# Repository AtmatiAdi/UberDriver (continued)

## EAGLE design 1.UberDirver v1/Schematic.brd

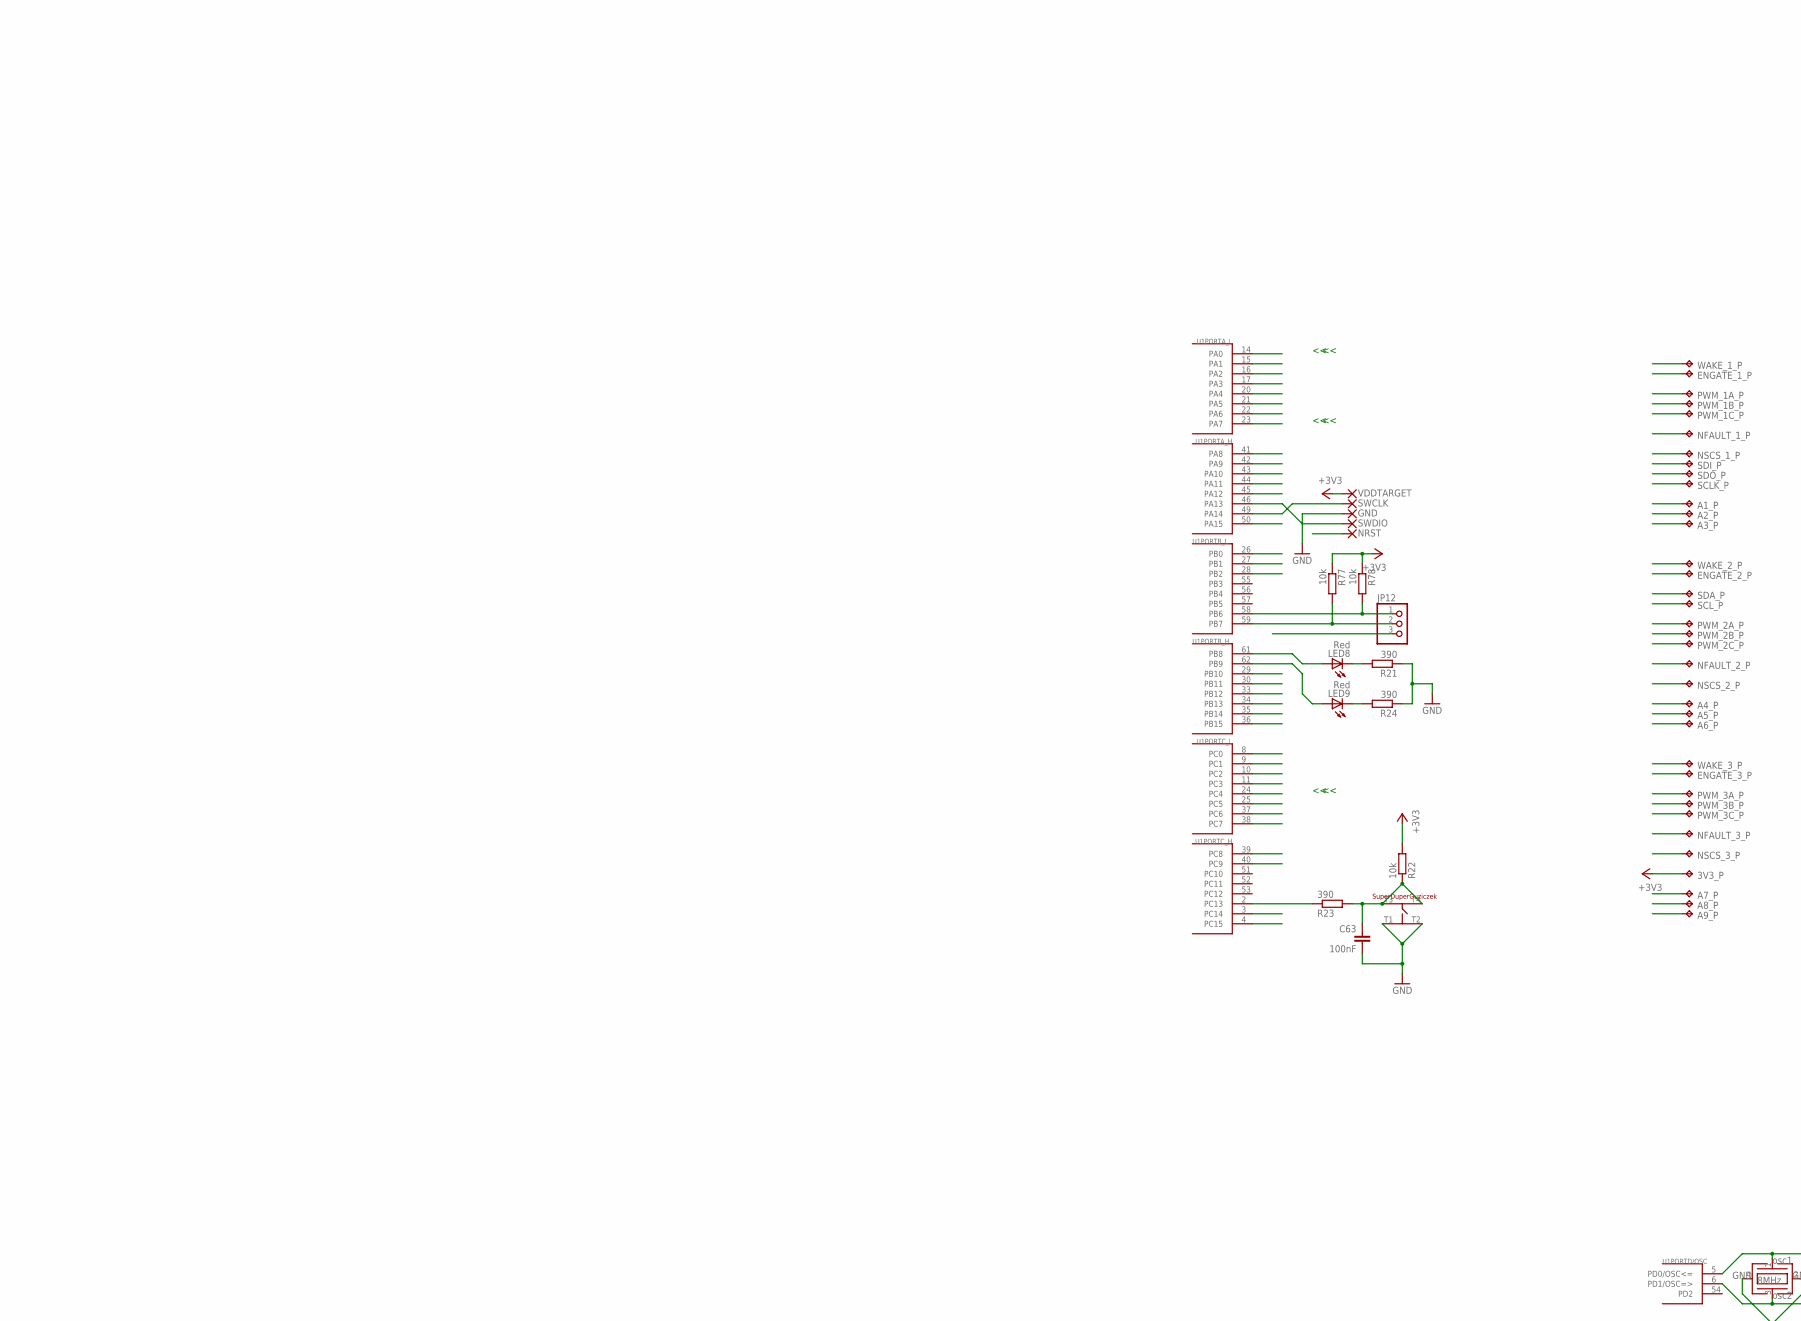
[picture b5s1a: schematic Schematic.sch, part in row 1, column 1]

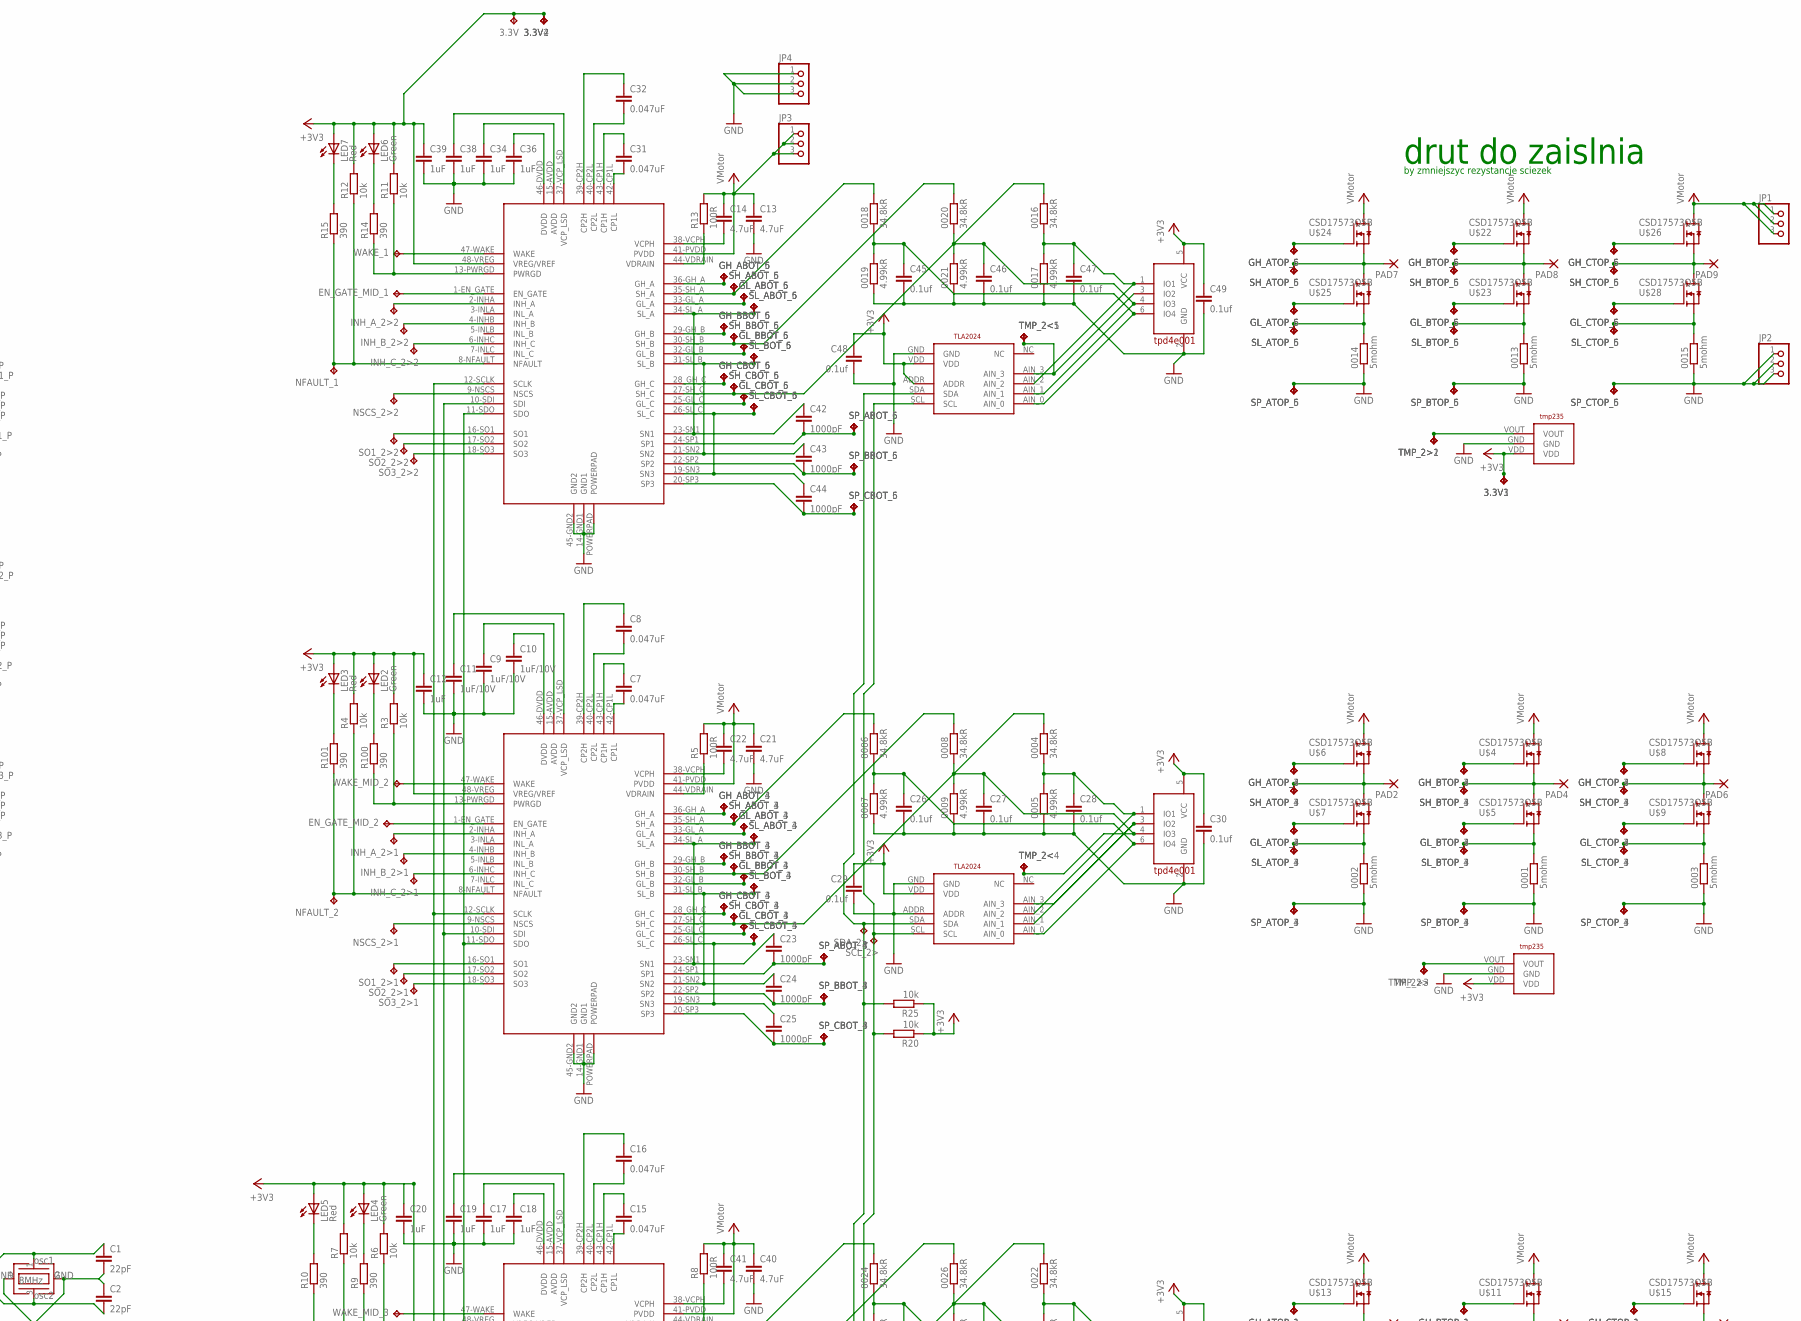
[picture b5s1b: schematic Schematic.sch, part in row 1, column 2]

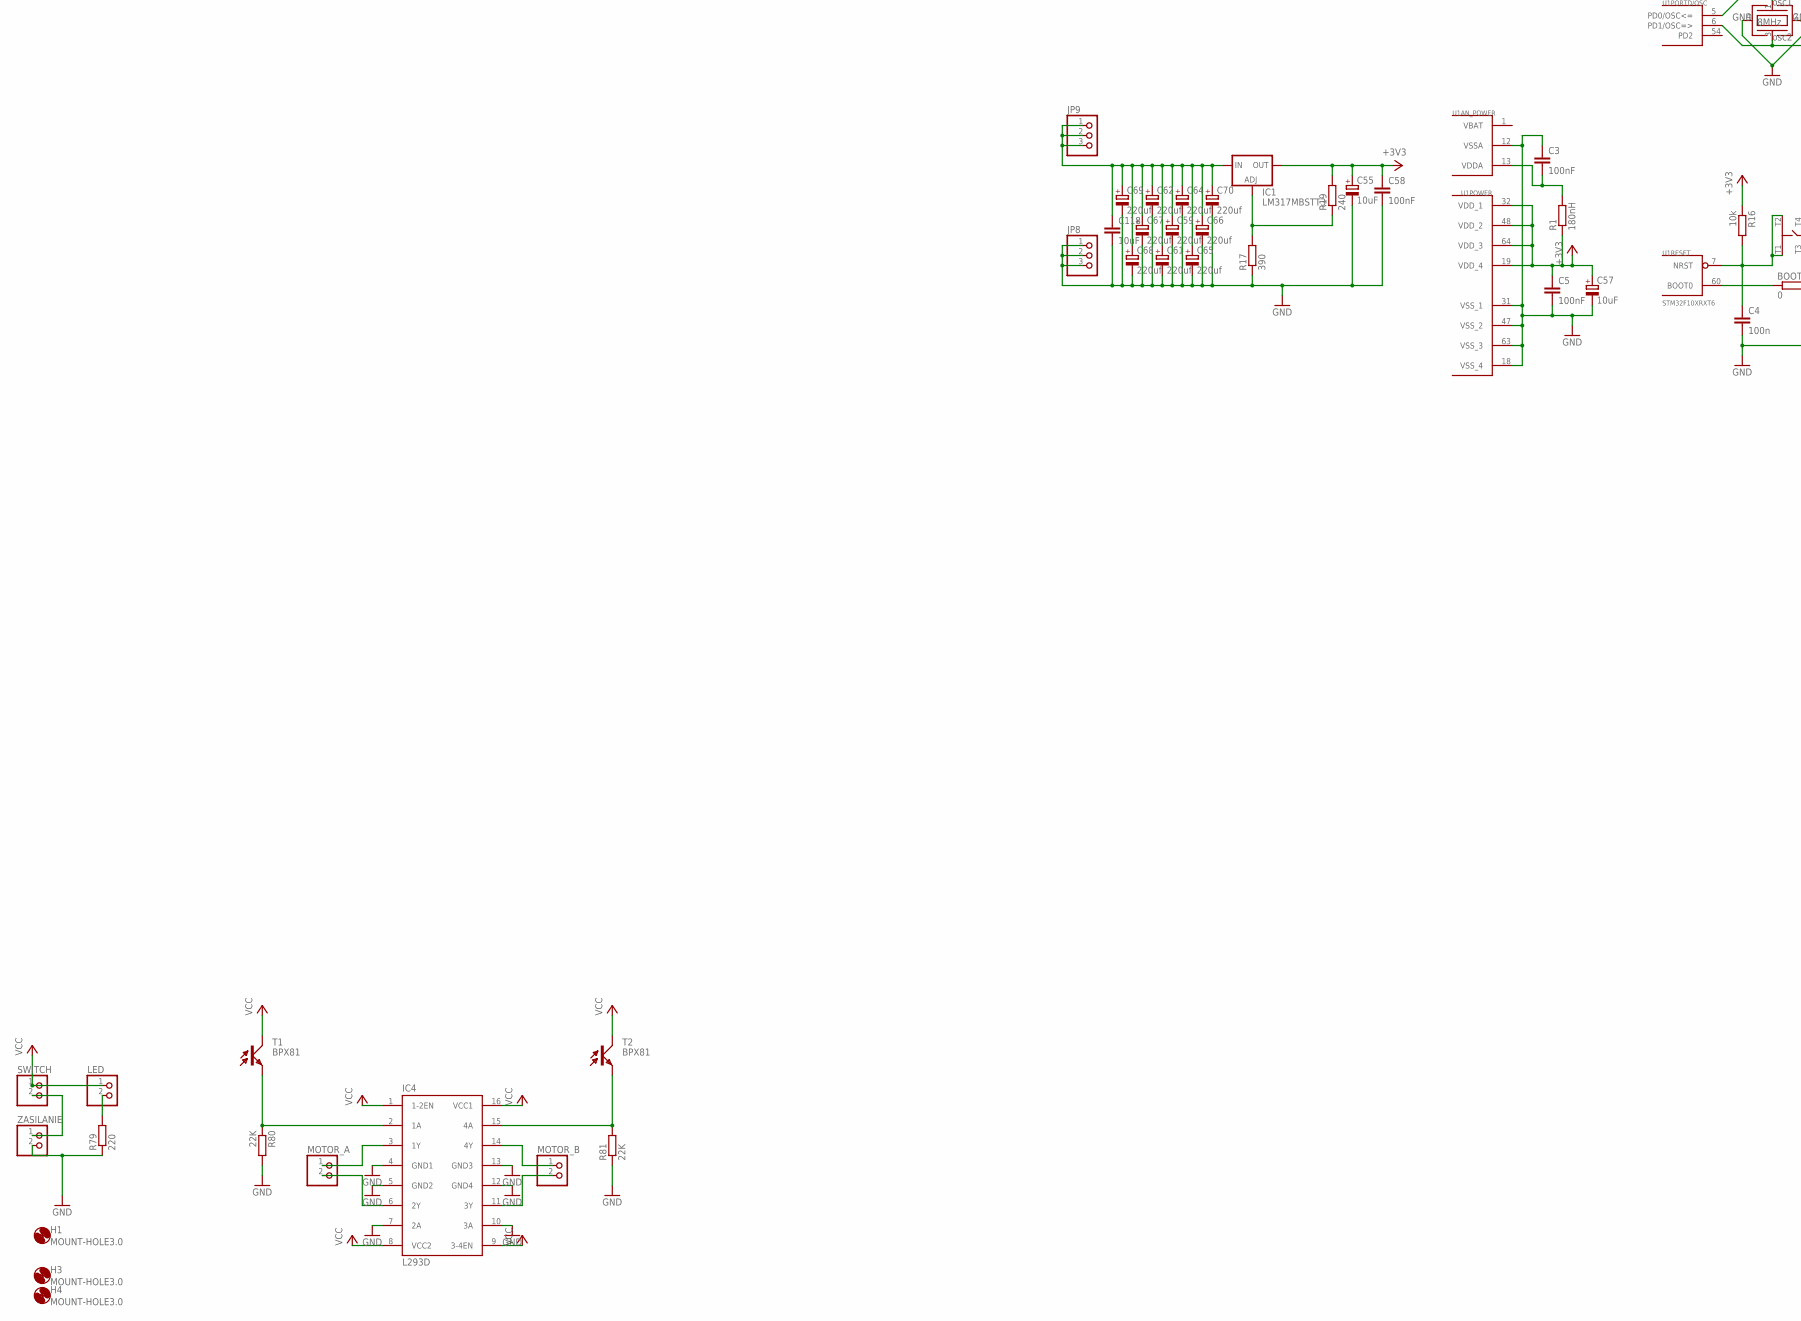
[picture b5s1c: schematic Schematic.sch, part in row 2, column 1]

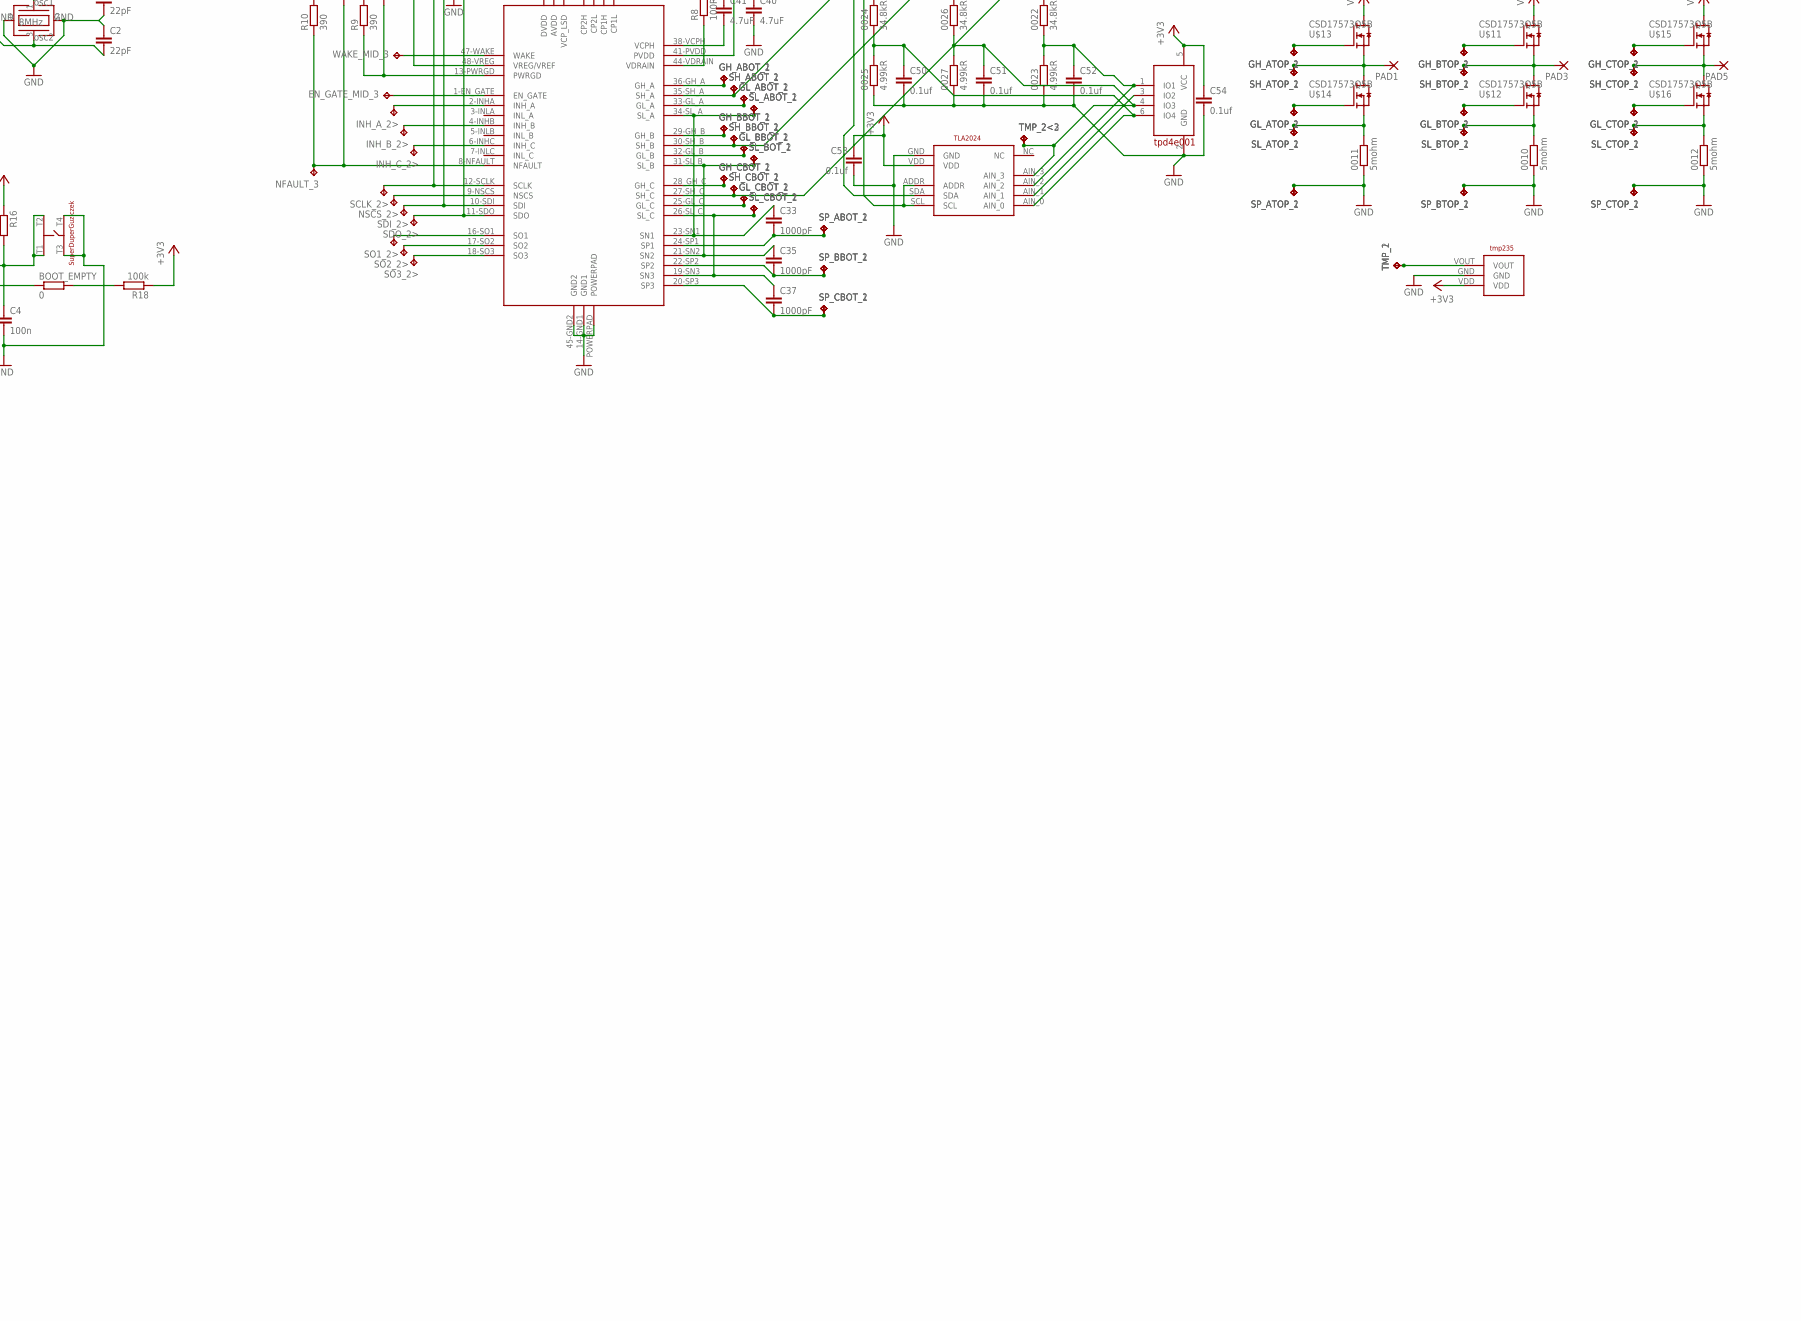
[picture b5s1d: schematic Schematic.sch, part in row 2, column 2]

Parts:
0001, 0002, 0003, 0010, 0011, 0012, 0013, 0014, 0015: 5mohm; R2512
3.3V, 3.3V1, 3.3V2, 3.3V3, 3.3V4, 3V3_P: TPTP09SQ; TP09SQ
0004, 0006, 0008, 0016, 0018, 0020, 0022, 0024, 0026: 34.8kR; R0603
0005, 0007, 0009, 0017, 0019, 0021, 0023, 0025, 0027: 4.99kR; R0603
A1_P, A2_P, A3_P, A4_P, A5_P, A6_P, A7_P, A8_P, A9_P: TPTP09SQ; TP09SQ
BOOT_EMPTY: 0; R0603
C1, C2: 22pF; C0603
C3, C5, C58, C63: 100nF; C0603
C4: 100n; C0603
C7, C8, C15, C16, C31, C32: 0.047uF; C0603
C9, C10, C11: 1uF/10V; C0603
C12, C17, C18, C19, C20, C34, C36, C38, C39: 1uF; C0603
C13, C14, C21, C22, C40, C41: 4.7uF; C0805
C23, C24, C25, C33, C35, C37, C42, C43, C44: 1000pF; C0603
C26, C27, C28, C29, C30, C45, C46, C47, C48, C49, C50, C51, C52, C53, C54: 0.1uf; C0603
C55, C57: 10uF; SMC_A
C59, C61, C62, C64, C65, C66, C67, C68, C69, C70: 220uf; 150CLZ-0810
C118: 10uF; C1206
ENGATE_1_P, ENGATE_2_P, ENGATE_3_P: TPTP09SQ; TP09SQ
EN_GATE_MID_1, EN_GATE_MID_2, EN_GATE_MID_3: TPTP09SQ; TP09SQ
GH_ABOT_1, GH_ABOT_2, GH_ABOT_3, GH_ABOT_4, GH_ABOT_5, GH_ABOT_6: TPTP09SQ; TP09SQ
GH_ATOP_1, GH_ATOP_2, GH_ATOP_3, GH_ATOP_4, GH_ATOP_5, GH_ATOP_6: TPTP09SQ; TP09SQ
GH_BBOT_1, GH_BBOT_2, GH_BBOT_3, GH_BBOT_4, GH_BBOT_5, GH_BBOT_6: TPTP07SQ; TP07SQ
GH_BTOP_1, GH_BTOP_2, GH_BTOP_3, GH_BTOP_4, GH_BTOP_5, GH_BTOP_6: TPTP07SQ; TP07SQ
GH_CBOT_1, GH_CBOT_2, GH_CBOT_3, GH_CBOT_4, GH_CBOT_5, GH_CBOT_6: TPTP09SQ; TP09SQ
GH_CTOP_1, GH_CTOP_2, GH_CTOP_3, GH_CTOP_4, GH_CTOP_5, GH_CTOP_6: TPTP09SQ; TP09SQ
GL_ABOT_1, GL_ABOT_2, GL_ABOT_3, GL_ABOT_4, GL_ABOT_5, GL_ABOT_6: TPTP07SQ; TP07SQ
GL_ATOP_1, GL_ATOP_2, GL_ATOP_3, GL_ATOP_4, GL_ATOP_5, GL_ATOP_6: TPTP07SQ; TP07SQ
GL_BBOT_1, GL_BBOT_2, GL_BBOT_3, GL_BBOT_4, GL_BBOT_5, GL_BBOT_6: TPTP09SQ; TP09SQ
GL_BTOP_1, GL_BTOP_2, GL_BTOP_3, GL_BTOP_4, GL_BTOP_5, GL_BTOP_6: TPTP09SQ; TP09SQ
GL_CBOT_1, GL_CBOT_2, GL_CBOT_3, GL_CBOT_4, GL_CBOT_5, GL_CBOT_6: TPTP07SQ; TP07SQ
GL_CTOP_1, GL_CTOP_2, GL_CTOP_3, GL_CTOP_4, GL_CTOP_5, GL_CTOP_6: TPTP07SQ; TP07SQ
GND: WIREPADSMD1,27-254; SMD1,27-2,54
H1, H3, H4: MOUNT-HOLE3.0; 3,0
IC1: LM317MBSTT3; SOT223
IC4: L293D; DIL16
INH_A_2>, INH_A_2>1, INH_A_2>2: TPTP09SQ; TP09SQ
INH_B_2>, INH_B_2>1, INH_B_2>2: TPTP09SQ; TP09SQ
INH_C_2>, INH_C_2>1, INH_C_2>2: TPTP09SQ; TP09SQ
JP1, JP2, JP3, JP4, JP8, JP9, JP12: PINHD-1X3; 1X03
LED: PINHD-1X2; 1X02
LED2, LED4, LED6: Green; SML0603
LED3, LED5, LED7, LED8, LED9: Red; SML0603
MOTOR_A: PINHD-1X2; 1X02
MOTOR_B: PINHD-1X2; 1X02
NFAULT_1, NFAULT_1_P, NFAULT_2, NFAULT_2_P, NFAULT_3, NFAULT_3_P: TPTP09SQ; TP09SQ
NRST: WIREPADSMD1,27-254; SMD1,27-2,54
NSCS_1_P, NSCS_2>, NSCS_2>1, NSCS_2>2, NSCS_2_P, NSCS_3_P: TPTP09SQ; TP09SQ
PAD1, PAD2, PAD3, PAD4, PAD5, PAD6, PAD7, PAD8, PAD9: SMD5; SMD2,54-5,08
PWM_1A_P, PWM_1B_P, PWM_1C_P, PWM_2A_P, PWM_2B_P, PWM_2C_P, PWM_3A_P, PWM_3B_P, PWM_3C_P: TPTP09SQ; TP09SQ
R1: 180nH; R0603
R3, R4, R6, R7, R11, R12, R16, R20, R22, R25, R77, R78: 10k; R0603
R5, R8, R13: 100R; R0603
R9, R10, R14, R15, R17, R21, R23, R24, R100, R101: 390; R0603
R18: 100k; R0603
R19: 240; R0603
R79: 220; R0805
R80, R81: 22K; R0805
SCLK_2>: TPTP09SQ; TP09SQ
SCLK_P: TPTP09SQ; TP09SQ
SCL_2>: TPTP09SQ; TP09SQ
SCL_P: TPTP09SQ; TP09SQ
SDA_2>: TPTP09SQ; TP09SQ
SDA_P: TPTP09SQ; TP09SQ
SDI_2>: TPTP09SQ; TP09SQ
SDI_P: TPTP09SQ; TP09SQ
SDO_2>: TPTP09SQ; TP09SQ
SDO_P: TPTP09SQ; TP09SQ
SH_ABOT_1, SH_ABOT_2, SH_ABOT_3, SH_ABOT_4, SH_ABOT_5, SH_ABOT_6: TPTP09SQ; TP09SQ
SH_ATOP_1, SH_ATOP_2, SH_ATOP_3, SH_ATOP_4, SH_ATOP_5, SH_ATOP_6: TPTP09SQ; TP09SQ
SH_BBOT_1, SH_BBOT_2, SH_BBOT_3, SH_BBOT_4, SH_BBOT_5, SH_BBOT_6: TPTP09SQ; TP09SQ
SH_BTOP_1, SH_BTOP_2, SH_BTOP_3, SH_BTOP_4, SH_BTOP_5, SH_BTOP_6: TPTP09SQ; TP09SQ
SH_CBOT_1, SH_CBOT_2, SH_CBOT_3, SH_CBOT_4, SH_CBOT_5, SH_CBOT_6: TPTP09SQ; TP09SQ
SH_CTOP_1, SH_CTOP_2, SH_CTOP_3, SH_CTOP_4, SH_CTOP_5, SH_CTOP_6: TPTP09SQ; TP09SQ
SL_ABOT_1, SL_ABOT_2, SL_ABOT_3, SL_ABOT_4, SL_ABOT_5, SL_ABOT_6: TPTP09SQ; TP09SQ
SL_ATOP_1, SL_ATOP_2, SL_ATOP_3, SL_ATOP_4, SL_ATOP_5, SL_ATOP_6: TPTP09SQ; TP09SQ
SL_BOT_1, SL_BOT_2, SL_BOT_3, SL_BOT_4, SL_BOT_5, SL_BOT_6: TPTP09SQ; TP09SQ
SL_BTOP_1, SL_BTOP_2, SL_BTOP_3, SL_BTOP_4, SL_BTOP_5, SL_BTOP_6: TPTP09SQ; TP09SQ
SL_CBOT_1, SL_CBOT_2, SL_CBOT_3, SL_CBOT_4, SL_CBOT_5, SL_CBOT_6: TPTP09SQ; TP09SQ
SL_CTOP_1, SL_CTOP_2, SL_CTOP_3, SL_CTOP_4, SL_CTOP_5, SL_CTOP_6: TPTP09SQ; TP09SQ
SO1_2>, SO1_2>1, SO1_2>2, SO2_2>, SO2_2>1, SO2_2>2, SO3_2>, SO3_2>1, SO3_2>2: TPTP09SQ; TP09SQ
SP_ABOT_1, SP_ABOT_2, SP_ABOT_3, SP_ABOT_4, SP_ABOT_5, SP_ABOT_6: TPTP09SQ; TP09SQ
SP_ATOP_1, SP_ATOP_2, SP_ATOP_3, SP_ATOP_4, SP_ATOP_5, SP_ATOP_6: TPTP09SQ; TP09SQ
SP_BBOT_1, SP_BBOT_2, SP_BBOT_3, SP_BBOT_4, SP_BBOT_5, SP_BBOT_6: TPTP09SQ; TP09SQ
SP_BTOP_1, SP_BTOP_2, SP_BTOP_3, SP_BTOP_4, SP_BTOP_5, SP_BTOP_6: TPTP09SQ; TP09SQ
SP_CBOT_1, SP_CBOT_2, SP_CBOT_3, SP_CBOT_4, SP_CBOT_5, SP_CBOT_6: TPTP09SQ; TP09SQ
SP_CTOP_1, SP_CTOP_2, SP_CTOP_3, SP_CTOP_4, SP_CTOP_5, SP_CTOP_6: TPTP09SQ; TP09SQ
SWCLK: WIREPADSMD1,27-254; SMD1,27-2,54
SWDIO: WIREPADSMD1,27-254; SMD1,27-2,54
SWITCH: PINHD-1X2; 1X02
T1, T2: BPX81
TMP_1, TMP_2, TMP_2<, TMP_2<1, TMP_2<2, TMP_2<3, TMP_2<4, TMP_2<5, TMP_2>, TMP_2>1, TMP_2>2, TMP_2>3: TPTP09SQ; TP09SQ
U1: STM32F10XRXT6; TQFP64
U$2, U$27: SUPER_DUPER_GUZICZEK
U$3, U$10, U$21: DRV8305; S-PQFP-G48
U$4, U$5, U$6, U$7, U$8, U$9, U$11, U$12, U$13, U$14, U$15, U$16, U$22, U$23, U$24, U$25, U$26, U$28: CSD17573Q5B; Q5B
U$17, U$29, U$32: TLA2024; X2QFN
U$18, U$19, U$30: TMP235; SOT-23
U$20, U$31, U$33: TPD4E001; SOT-23
U$35: 8MHZ; SMD
VDDTARGET: WIREPADSMD1,27-254; SMD1,27-2,54
WAKE_1, WAKE_1_P, WAKE_2_P, WAKE_3_P: TPTP09SQ; TP09SQ
WAKE_MID_2, WAKE_MID_3: TPTP09SQ; TP09SQ
ZASILANIE: PINHD-1X2; 1X02

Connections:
+3V3: 3.3V.TP, 3.3V1.TP, 3.3V2.TP, 3.3V3.TP, 3.3V4.TP, 3V3_P.TP, C5.1, C12.1, C20.1, C29.1, C30.1, C39.1, C48.1, C49.1, C53.1, C54.1, C55.+, C57.+, C58.1, IC1.4 (OUT), LED2.A, LED3.A, LED4.A, LED5.A, LED6.A, LED7.A, R1.1, R3.2, R4.2, R6.2, R7.2, R11.2, R12.2, R16.1, R18.1, R19.2, R20.1, R22.2, R25.1, R77.1, R78.1, U1.19 (VDD_4), U1.32 (VDD_1), U1.48 (VDD_2), U1.64 (VDD_3), U$3.48-VREG (VREG/VREF), U$10.48-VREG (VREG/VREF), U$17.VDD, U$18.VDD, U$19.VDD, U$20.5 (VCC), U$21.48-VREG (VREG/VREF), U$29.ADDR, U$29.VDD, U$30.VDD, U$31.5 (VCC), U$32.VDD, U$33.5 (VCC), VDDTARGET.1
A1: A1_P.TP, U1.25 (PC5)
A2: A2_P.TP, U1.26 (PB0)
A3: A3_P.TP, U1.27 (PB1)
A4: A4_P.TP, U1.22 (PA6)
A5: A5_P.TP, U1.21 (PA5)
A6: A6_P.TP, U1.20 (PA4)
A7: A7_P.TP, U1.10 (PC2)
A8: A8_P.TP, U1.9 (PC1)
A9: A9_P.TP, U1.8 (PC0)
AIN1: 0006.1, 0007.2, C26.1, U$17.AIN_0, U$20.6 (IO4)
AIN3: 0004.1, 0005.2, C28.1, U$17.AIN_2, U$20.1 (IO1)
AIN5: 0016.1, 0017.2, C47.1, U$29.AIN_2, U$31.1 (IO1)
AIN6: 0018.1, 0019.2, C45.1, U$29.AIN_0, U$31.6 (IO4)
AIN7: 0020.1, 0021.2, C46.1, U$29.AIN_1, U$31.4 (IO3)
AIN9: 0022.1, 0023.2, C52.1, U$32.AIN_2, U$33.1 (IO1)
AIN10: 0024.1, 0025.2, C50.1, U$32.AIN_0, U$33.6 (IO4)
AIN11: 0026.1, 0027.2, C51.1, U$32.AIN_1, U$33.4 (IO3)
ENGATE_1: ENGATE_1_P.TP, U1.44 (PA11)
ENGATE_2: ENGATE_2_P.TP, U1.28 (PB2)
ENGATE_3: ENGATE_3_P.TP, U1.4 (PC15)
EN_GATE_MID_1: EN_GATE_MID_1.TP, U$21.1-EN_GATE (EN_GATE)
EN_GATE_MID_2: EN_GATE_MID_2.TP, U$3.1-EN_GATE (EN_GATE)
EN_GATE_MID_3: EN_GATE_MID_3.TP, U$10.1-EN_GATE (EN_GATE)
GH_ABOT_1: GH_ABOT_1.TP, GH_ABOT_2.TP, U$10.36-GH_A (GH_A)
GH_ABOT_2: GH_ABOT_3.TP, GH_ABOT_4.TP, U$3.36-GH_A (GH_A)
GH_ABOT_3: GH_ABOT_5.TP, GH_ABOT_6.TP, U$21.36-GH_A (GH_A)
GH_ATOP_1: GH_ATOP_1.TP, GH_ATOP_2.TP, U$13.G
GH_ATOP_2: GH_ATOP_5.TP, GH_ATOP_6.TP, U$24.G
GH_ATOP_4: GH_ATOP_3.TP, GH_ATOP_4.TP, U$6.G
GH_BBOT_1: GH_BBOT_1.TP, GH_BBOT_2.TP, U$10.29-GH_B (GH_B)
GH_BBOT_2: GH_BBOT_3.TP, GH_BBOT_4.TP, U$3.29-GH_B (GH_B)
GH_BBOT_3: GH_BBOT_5.TP, GH_BBOT_6.TP, U$21.29-GH_B (GH_B)
GH_BTOP_1: GH_BTOP_1.TP, GH_BTOP_2.TP, U$11.G
GH_BTOP_2: GH_BTOP_5.TP, GH_BTOP_6.TP, U$22.G
GH_BTOP_4: GH_BTOP_3.TP, GH_BTOP_4.TP, U$4.G
GH_CBOT_1: GH_CBOT_1.TP, GH_CBOT_2.TP, U$10.28_GH_C (GH_C)
GH_CBOT_2: GH_CBOT_3.TP, GH_CBOT_4.TP, U$3.28_GH_C (GH_C)
GH_CBOT_3: GH_CBOT_5.TP, GH_CBOT_6.TP, U$21.28_GH_C (GH_C)
GH_CTOP_1: GH_CTOP_5.TP, GH_CTOP_6.TP, U$26.G
GH_CTOP_4: GH_CTOP_3.TP, GH_CTOP_4.TP, U$8.G
GH_C_2>: GH_CTOP_1.TP, GH_CTOP_2.TP, U$15.G
GL_ABOT_1: GL_ABOT_1.TP, GL_ABOT_2.TP, U$10.33-GL_A (GL_A)
GL_ABOT_2: GL_ABOT_3.TP, GL_ABOT_4.TP, U$3.33-GL_A (GL_A)
GL_ABOT_3: GL_ABOT_5.TP, GL_ABOT_6.TP, U$21.33-GL_A (GL_A)
GL_ATOP_1: GL_ATOP_1.TP, GL_ATOP_2.TP, U$14.G
GL_ATOP_2: GL_ATOP_5.TP, GL_ATOP_6.TP, U$25.G
GL_ATOP_4: GL_ATOP_3.TP, GL_ATOP_4.TP, U$7.G
GL_BBOT_1: GL_BBOT_1.TP, GL_BBOT_2.TP, U$10.32-GL_B (GL_B)
GL_BBOT_2: GL_BBOT_3.TP, GL_BBOT_4.TP, U$3.32-GL_B (GL_B)
GL_BBOT_3: GL_BBOT_5.TP, GL_BBOT_6.TP, U$21.32-GL_B (GL_B)
GL_BTOP_1: GL_BTOP_1.TP, GL_BTOP_2.TP, U$12.G
GL_BTOP_2: GL_BTOP_5.TP, GL_BTOP_6.TP, U$23.G
GL_BTOP_4: GL_BTOP_3.TP, GL_BTOP_4.TP, U$5.G
GL_CBOT_1: GL_CBOT_1.TP, GL_CBOT_2.TP, U$10.25-GL_C (GL_C)
GL_CBOT_2: GL_CBOT_3.TP, GL_CBOT_4.TP, U$3.25-GL_C (GL_C)
GL_CBOT_3: GL_CBOT_5.TP, GL_CBOT_6.TP, U$21.25-GL_C (GL_C)
GL_CTOP_1: GL_CTOP_5.TP, GL_CTOP_6.TP, U$28.G
GL_CTOP_4: GL_CTOP_3.TP, GL_CTOP_4.TP, U$9.G
GND: 0005.1, 0007.1, 0009.1, 0017.1, 0019.1, 0021.1, 0023.1, 0025.1, 0027.1, C1.2, C2.1, C3.1, C4.2, C5.2, C9.2, C10.2, C11.2, C12.2, C13.2, C17.2, C18.2, C19.2, C20.2, C21.2, C26.2, C27.2, C28.2, C29.2, C30.2, C34.2, C36.2, C38.2, C39.2, C40.2, C45.2, C46.2, C47.2, C48.2, C49.2, C50.2, C51.2, C52.2, C53.2, C54.2, C55.-, C57.-, C58.2, C59.-, C61.-, C62.-, C63.2, C64.-, C65.-, C66.-, C67.-, C68.-, C69.-, C70.-, C118.2, GND.1, IC4.4 (GND1), IC4.5 (GND2), IC4.7 (2A), IC4.10 (3A), IC4.12 (GND4), IC4.13 (GND3), JP4.1, JP4.2, JP4.3, JP8.1, JP8.2, JP8.3, R17.1, R21.1, R24.1, R79.1, R80.2, R81.1, U1.12 (VSSA), U1.18 (VSS_4), U1.31 (VSS_1), U1.47 (VSS_2), U1.63 (VSS_3), U$2.T1, U$2.T2, U$3.14-GND1 (GND1), U$3.45-GND2 (GND2), U$3.POWERPAD, U$10.14-GND1 (GND1), U$10.45-GND2 (GND2), U$10.POWERPAD, U$17.ADDR, U$17.GND, U$20.2 (GND), U$21.14-GND1 (GND1), U$21.45-GND2 (GND2), U$21.POWERPAD, U$27.T3, U$27.T4, U$29.GND, U$31.2 (GND), U$32.GND, U$33.2 (GND), U$35.2 (GND2), U$35.4 (GND1), ZASILANIE.2
GND_TOP: 0001.1, 0002.1, 0003.1, 0010.1, 0011.1, 0012.1, 0013.1, 0014.1, 0015.1, JP2.1, JP2.2, JP2.3, SP_ATOP_1.TP, SP_ATOP_2.TP, SP_ATOP_3.TP, SP_ATOP_4.TP, SP_ATOP_5.TP, SP_ATOP_6.TP, SP_BTOP_1.TP, SP_BTOP_2.TP, SP_BTOP_3.TP, SP_BTOP_4.TP, SP_BTOP_5.TP, SP_BTOP_6.TP, SP_CTOP_1.TP, SP_CTOP_2.TP, SP_CTOP_3.TP, SP_CTOP_4.TP, SP_CTOP_5.TP, SP_CTOP_6.TP, U$18.GND, U$19.GND, U$30.GND
INH_A_2>: INH_A_2>.TP, U$10.2-INHA (INH_A)
INH_A_2>1: INH_A_2>1.TP, U$3.2-INHA (INH_A)
INH_A_2>2: INH_A_2>2.TP, U$21.2-INHA (INH_A)
INH_B_2>: INH_B_2>.TP, U$10.4-INHB (INH_B)
INH_B_2>1: INH_B_2>1.TP, U$3.4-INHB (INH_B)
INH_B_2>2: INH_B_2>2.TP, U$21.4-INHB (INH_B)
INH_C_2>: INH_C_2>.TP, U$10.6-INHC (INH_C)
INH_C_2>1: INH_C_2>1.TP, U$3.6-INHC (INH_C)
INH_C_2>2: INH_C_2>2.TP, U$21.6-INHC (INH_C)
unnamed: C10.1, U$3.46-DVDD (DVDD)
unnamed: C9.1, U$3.15-AVDD (AVDD)
unnamed: LED8.C, R21.2
unnamed: C11.1, U$3.37-VCP_LSD (VCP_LSD)
unnamed: C7.2, U$3.42-CP1L (CP1L)
unnamed: C7.1, U$3.43-CP1H (CP1H)
unnamed: C8.2, U$3.40-CP2L (CP2L)
unnamed: C8.1, U$3.39-CP2H (CP2H)
unnamed: R5.1, U$3.44-VDRAIN (VDRAIN)
unnamed: C36.1, U$21.46-DVDD (DVDD)
unnamed: C22.2, U$3.38-VCPH (VCPH)
unnamed: C34.1, U$21.15-AVDD (AVDD)
unnamed: C38.1, U$21.37-VCP_LSD (VCP_LSD)
unnamed: C31.2, U$21.42-CP1L (CP1L)
unnamed: LED2.C, R100.2
unnamed: C31.1, U$21.43-CP1H (CP1H)
unnamed: LED3.C, R101.2
unnamed: LED4.C, R9.2
unnamed: LED5.C, R10.2
unnamed: C32.2, U$21.40-CP2L (CP2L)
unnamed: C32.1, U$21.39-CP2H (CP2H)
unnamed: R13.1, U$21.44-VDRAIN (VDRAIN)
unnamed: C14.2, U$21.38-VCPH (VCPH)
unnamed: LED6.C, R14.2
unnamed: LED7.C, R15.2
unnamed: TMP_2<2.TP, TMP_2<3.TP, U$32.AIN_3, U$33.3 (IO2)
unnamed: TMP_2<.TP, TMP_2<4.TP, U$17.AIN_3, U$20.3 (IO2)
unnamed: 0008.1, 0009.2, C27.1, U$17.AIN_1, U$20.4 (IO3)
unnamed: R23.1, U1.2 (PC13)
unnamed: TMP_2<1.TP, TMP_2<5.TP, U$29.AIN_3, U$31.3 (IO2)
unnamed: LED8.A, U1.61 (PB8)
unnamed: SWCLK.1, U1.49 (PA14)
unnamed: SWDIO.1, U1.46 (PA13)
unnamed: LED9.A, U1.62 (PB9)
unnamed: SWITCH.2, ZASILANIE.1
unnamed: BOOT_EMPTY.2, R18.2
unnamed: BOOT_EMPTY.1, U1.60 (BOOT0)
unnamed: IC4.2 (1A), R80.1, T1.E
unnamed: IC4.15 (4A), R81.2, T2.E
unnamed: IC4.14 (4Y), MOTOR_B.1
unnamed: IC4.11 (3Y), MOTOR_B.2
unnamed: IC4.3 (1Y), MOTOR_A.1
unnamed: IC4.6 (2Y), MOTOR_A.2
unnamed: LED.2, R79.2
unnamed: C3.2, R1.2, U1.13 (VDDA)
unnamed: C18.1, U$10.46-DVDD (DVDD)
unnamed: C17.1, U$10.15-AVDD (AVDD)
unnamed: C19.1, U$10.37-VCP_LSD (VCP_LSD)
unnamed: C15.2, U$10.42-CP1L (CP1L)
unnamed: C15.1, U$10.43-CP1H (CP1H)
unnamed: C16.2, U$10.40-CP2L (CP2L)
unnamed: C16.1, U$10.39-CP2H (CP2H)
unnamed: GL_CTOP_1.TP, GL_CTOP_2.TP, U$16.G
unnamed: IC1.1 (ADJ), R17.2, R19.1
unnamed: C63.1, R22.1, R23.2, U$2.T3, U$2.T4
unnamed: LED9.C, R24.2
unnamed: R8.1, U$10.44-VDRAIN (VDRAIN)
unnamed: C41.2, U$10.38-VCPH (VCPH)
NFAULT: NFAULT_3.TP, R7.1, R10.1, U$10.8-NFAULT (NFAULT)
NFAULT1: NFAULT_2.TP, R4.1, R101.1, U$3.8-NFAULT (NFAULT)
NFAULT2: NFAULT_1.TP, R12.1, R15.1, U$21.8-NFAULT (NFAULT)
NFAULT_1: NFAULT_1_P.TP, U1.50 (PA15)
NFAULT_2: NFAULT_2_P.TP, U1.24 (PC4)
NFAULT_3: NFAULT_3_P.TP, U1.14 (PA0)
NRST: C4.1, JP12.3, NRST.1, R16.2, U1.7 (NRST), U$27.T1, U$27.T2
NSCS_1: NSCS_1_P.TP, U1.33 (PB12)
NSCS_2: NSCS_2_P.TP, U1.23 (PA7)
NSCS_2>: NSCS_2>.TP, U$10.9-NSCS (NSCS)
NSCS_2>1: NSCS_2>1.TP, U$3.9-NSCS (NSCS)
NSCS_2>2: NSCS_2>2.TP, U$21.9-NSCS (NSCS)
NSCS_3: NSCS_3_P.TP, U1.11 (PC3)
OSC1: C1.1, U1.5 (PD0/OSC<=), U$35.1
OSC2: C2.2, U1.6 (PD1/OSC=>), U$35.3 (2)
PWM_1A: PWM_1A_P.TP, U1.43 (PA10)
PWM_1B: PWM_1B_P.TP, U1.42 (PA9)
PWM_1C: PWM_1C_P.TP, U1.41 (PA8)
PWM_2A: PWM_2A_P.TP, U1.37 (PC6)
PWM_2B: PWM_2B_P.TP, U1.38 (PC7)
PWM_2C: PWM_2C_P.TP, U1.39 (PC8)
PWM_3A: PWM_3A_P.TP, U1.17 (PA3)
PWM_3B: PWM_3B_P.TP, U1.16 (PA2)
PWM_3C: PWM_3C_P.TP, U1.15 (PA1)
PWRGD: R6.1, R9.1, U$10.13-PWRGD (PWRGD)
PWRGD1: R3.1, R100.1, U$3.13-PWRGD (PWRGD)
PWRGD2: R11.1, R14.1, U$21.13-PWRGD (PWRGD)
SCL: SCL_P.TP, U1.29 (PB10)
SCLK: SCLK_P.TP, U1.34 (PB13)
SCLK_2>: SCLK_2>.TP, U$3.12-SCLK (SCLK), U$10.12-SCLK (SCLK), U$21.12-SCLK (SCLK)
SCL_2>: R20.2, SCL_2>.TP, U$17.SCL, U$29.SCL, U$32.ADDR, U$32.SCL
SCL_DRIVER: JP12.1, R78.2, U1.58 (PB6)
SDA: SDA_P.TP, U1.30 (PB11)
SDA_2>: R25.2, SDA_2>.TP, U$17.SDA, U$29.SDA, U$32.SDA
SDA_DRIVER: JP12.2, R77.2, U1.59 (PB7)
SDI: SDI_P.TP, U1.36 (PB15)
SDI_2>: SDI_2>.TP, U$3.10-SDI (SDI), U$10.10-SDI (SDI), U$21.10-SDI (SDI)
SDO: SDO_P.TP, U1.35 (PB14)
SDO_2>: SDO_2>.TP, U$3.11-SDO (SDO), U$10.11-SDO (SDO), U$21.11-SDO (SDO)
SH_ABOT_1: 0024.2, SH_ABOT_1.TP, SH_ABOT_2.TP, U$10.35-SH_A (SH_A)
SH_ABOT_2: 0006.2, SH_ABOT_3.TP, SH_ABOT_4.TP, U$3.35-SH_A (SH_A)
SH_ABOT_3: 0018.2, SH_ABOT_5.TP, SH_ABOT_6.TP, U$21.35-SH_A (SH_A)
SH_ATOP_1: PAD1.1, SH_ATOP_1.TP, SH_ATOP_2.TP, U$13.S1 (S), U$13.S2 (S), U$13.S3 (S), U$14.D1 (D), U$14.D2 (D), U$14.D3 (D), U$14.D4 (D), U$14.D5 (D)
SH_ATOP_2: PAD7.1, SH_ATOP_5.TP, SH_ATOP_6.TP, U$24.S1 (S), U$24.S2 (S), U$24.S3 (S), U$25.D1 (D), U$25.D2 (D), U$25.D3 (D), U$25.D4 (D), U$25.D5 (D)
SH_ATOP_4: PAD2.1, SH_ATOP_3.TP, SH_ATOP_4.TP, U$6.S1 (S), U$6.S2 (S), U$6.S3 (S), U$7.D1 (D), U$7.D2 (D), U$7.D3 (D), U$7.D4 (D), U$7.D5 (D)
SH_BBOT_1: 0026.2, SH_BBOT_1.TP, SH_BBOT_2.TP, U$10.30-SH_B (SH_B)
SH_BBOT_2: 0008.2, SH_BBOT_3.TP, SH_BBOT_4.TP, U$3.30-SH_B (SH_B)
SH_BBOT_3: 0020.2, SH_BBOT_5.TP, SH_BBOT_6.TP, U$21.30-SH_B (SH_B)
SH_BTOP_1: PAD3.1, SH_BTOP_1.TP, SH_BTOP_2.TP, U$11.S1 (S), U$11.S2 (S), U$11.S3 (S), U$12.D1 (D), U$12.D2 (D), U$12.D3 (D), U$12.D4 (D), U$12.D5 (D)
SH_BTOP_2: PAD8.1, SH_BTOP_5.TP, SH_BTOP_6.TP, U$22.S1 (S), U$22.S2 (S), U$22.S3 (S), U$23.D1 (D), U$23.D2 (D), U$23.D3 (D), U$23.D4 (D), U$23.D5 (D)
SH_BTOP_4: PAD4.1, SH_BTOP_3.TP, SH_BTOP_4.TP, U$4.S1 (S), U$4.S2 (S), U$4.S3 (S), U$5.D1 (D), U$5.D2 (D), U$5.D3 (D), U$5.D4 (D), U$5.D5 (D)
SH_CBOT_1: 0022.2, SH_CBOT_1.TP, SH_CBOT_2.TP, U$10.27-SH_C (SH_C)
SH_CBOT_2: 0004.2, SH_CBOT_3.TP, SH_CBOT_4.TP, U$3.27-SH_C (SH_C)
SH_CBOT_3: 0016.2, SH_CBOT_5.TP, SH_CBOT_6.TP, U$21.27-SH_C (SH_C)
SH_CTOP_1: PAD9.1, SH_CTOP_5.TP, SH_CTOP_6.TP, U$26.S1 (S), U$26.S2 (S), U$26.S3 (S), U$28.D1 (D), U$28.D2 (D), U$28.D3 (D), U$28.D4 (D), U$28.D5 (D)
SH_CTOP_4: PAD6.1, SH_CTOP_3.TP, SH_CTOP_4.TP, U$8.S1 (S), U$8.S2 (S), U$8.S3 (S), U$9.D1 (D), U$9.D2 (D), U$9.D3 (D), U$9.D4 (D), U$9.D5 (D)
SH_C_2>: PAD5.1, SH_CTOP_1.TP, SH_CTOP_2.TP, U$15.S1 (S), U$15.S2 (S), U$15.S3 (S), U$16.D1 (D), U$16.D2 (D), U$16.D3 (D), U$16.D4 (D), U$16.D5 (D)
SL_ABOT_1: C33.1, SL_ABOT_1.TP, SL_ABOT_2.TP, U$10.23-SN1 (SN1), U$10.34-SL_A (SL_A)
SL_ABOT_2: C23.1, SL_ABOT_3.TP, SL_ABOT_4.TP, U$3.23-SN1 (SN1), U$3.34-SL_A (SL_A)
SL_ABOT_3: C42.1, SL_ABOT_5.TP, SL_ABOT_6.TP, U$21.23-SN1 (SN1), U$21.34-SL_A (SL_A)
SL_ATOP_1: 0011.2, SL_ATOP_1.TP, SL_ATOP_2.TP, U$14.S1 (S), U$14.S2 (S), U$14.S3 (S)
SL_ATOP_2: 0014.2, SL_ATOP_5.TP, SL_ATOP_6.TP, U$25.S1 (S), U$25.S2 (S), U$25.S3 (S)
SL_ATOP_4: 0002.2, SL_ATOP_3.TP, SL_ATOP_4.TP, U$7.S1 (S), U$7.S2 (S), U$7.S3 (S)
SL_BOT_1: C35.1, SL_BOT_1.TP, SL_BOT_2.TP, U$10.21-SN2 (SN2), U$10.31-SL_B (SL_B)
SL_BOT_2: C24.1, SL_BOT_3.TP, SL_BOT_4.TP, U$3.21-SN2 (SN2), U$3.31-SL_B (SL_B)
SL_BOT_3: C43.1, SL_BOT_5.TP, SL_BOT_6.TP, U$21.21-SN2 (SN2), U$21.31-SL_B (SL_B)
SL_BTOP_1: 0010.2, SL_BTOP_1.TP, SL_BTOP_2.TP, U$12.S1 (S), U$12.S2 (S), U$12.S3 (S)
SL_BTOP_2: 0013.2, SL_BTOP_5.TP, SL_BTOP_6.TP, U$23.S1 (S), U$23.S2 (S), U$23.S3 (S)
SL_BTOP_4: 0001.2, SL_BTOP_3.TP, SL_BTOP_4.TP, U$5.S1 (S), U$5.S2 (S), U$5.S3 (S)
SL_CBOT_1: C37.1, SL_CBOT_1.TP, SL_CBOT_2.TP, U$10.19-SN3 (SN3), U$10.26-SL_C (SL_C)
SL_CBOT_2: C25.1, SL_CBOT_3.TP, SL_CBOT_4.TP, U$3.19-SN3 (SN3), U$3.26-SL_C (SL_C)
SL_CTOP_1: 0015.2, SL_CTOP_5.TP, SL_CTOP_6.TP, U$28.S1 (S), U$28.S2 (S), U$28.S3 (S)
SL_CTOP_4: 0003.2, SL_CTOP_3.TP, SL_CTOP_4.TP, U$9.S1 (S), U$9.S2 (S), U$9.S3 (S)
SL_C_2<2: C44.1, SL_CBOT_5.TP, SL_CBOT_6.TP, U$21.19-SN3 (SN3), U$21.26-SL_C (SL_C)
SL_C_2>: 0012.2, SL_CTOP_1.TP, SL_CTOP_2.TP, U$16.S1 (S), U$16.S2 (S), U$16.S3 (S)
SO1_2>: SO1_2>.TP, U$10.16-SO1 (SO1)
SO1_2>1: SO1_2>1.TP, U$3.16-SO1 (SO1)
SO1_2>2: SO1_2>2.TP, U$21.16-SO1 (SO1)
SO2_2>: SO2_2>.TP, U$10.17-SO2 (SO2)
SO2_2>1: SO2_2>1.TP, U$3.17-SO2 (SO2)
SO2_2>2: SO2_2>2.TP, U$21.17-SO2 (SO2)
SO3_2>: SO3_2>.TP, U$10.18-SO3 (SO3)
SO3_2>1: SO3_2>1.TP, U$3.18-SO3 (SO3)
SO3_2>2: SO3_2>2.TP, U$21.18-SO3 (SO3)
SP_ABOT_1: C33.2, SP_ABOT_1.TP, SP_ABOT_2.TP, U$10.24-SP1 (SP1)
SP_ABOT_2: C23.2, SP_ABOT_3.TP, SP_ABOT_4.TP, U$3.24-SP1 (SP1)
SP_ABOT_3: C42.2, SP_ABOT_5.TP, SP_ABOT_6.TP, U$21.24-SP1 (SP1)
SP_BBOT_1: C35.2, SP_BBOT_1.TP, SP_BBOT_2.TP, U$10.22-SP2 (SP2)
SP_BBOT_2: C24.2, SP_BBOT_3.TP, SP_BBOT_4.TP, U$3.22-SP2 (SP2)
SP_BBOT_3: C43.2, SP_BBOT_5.TP, SP_BBOT_6.TP, U$21.22-SP2 (SP2)
SP_CBOT_1: C37.2, SP_CBOT_1.TP, SP_CBOT_2.TP, U$10.20-SP3 (SP3)
SP_CBOT_2: C25.2, SP_CBOT_3.TP, SP_CBOT_4.TP, U$3.20-SP3 (SP3)
SP_CBOT_3: C44.2, SP_CBOT_5.TP, SP_CBOT_6.TP, U$21.20-SP3 (SP3)
TMP_1: TMP_1.TP, TMP_2.TP, U$18.VOUT
TMP_2>: TMP_2>.TP, TMP_2>3.TP, U$19.VOUT
TMP_2>1: TMP_2>1.TP, TMP_2>2.TP, U$30.VOUT
VBAT: U1.1 (VBAT)
VCC: IC4.1 (1-2EN), IC4.8 (VCC2), IC4.9 (3-4EN), IC4.16 (VCC1), LED.1, SWITCH.1, T1.C, T2.C
VMOTOR: C13.1, C14.1, C21.1, C22.1, C40.1, C41.1, JP3.1, JP3.2, JP3.3, R5.2, R8.2, R13.2, U$3.41-PVDD (PVDD), U$10.41-PVDD (PVDD), U$21.41-PVDD (PVDD)
VMOTOR_BOTTOM: C59.+, C61.+, C62.+, C64.+, C65.+, C66.+, C67.+, C68.+, C69.+, C70.+, C118.1, IC1.3 (IN), JP9.1, JP9.2, JP9.3
VMOTOR_TOP: JP1.1, JP1.2, JP1.3, U$4.D1 (D), U$4.D2 (D), U$4.D3 (D), U$4.D4 (D), U$4.D5 (D), U$6.D1 (D), U$6.D2 (D), U$6.D3 (D), U$6.D4 (D), U$6.D5 (D), U$8.D1 (D), U$8.D2 (D), U$8.D3 (D), U$8.D4 (D), U$8.D5 (D), U$11.D1 (D), U$11.D2 (D), U$11.D3 (D), U$11.D4 (D), U$11.D5 (D), U$13.D1 (D), U$13.D2 (D), U$13.D3 (D), U$13.D4 (D), U$13.D5 (D), U$15.D1 (D), U$15.D2 (D), U$15.D3 (D), U$15.D4 (D), U$15.D5 (D), U$22.D1 (D), U$22.D2 (D), U$22.D3 (D), U$22.D4 (D), U$22.D5 (D), U$24.D1 (D), U$24.D2 (D), U$24.D3 (D), U$24.D4 (D), U$24.D5 (D), U$26.D1 (D), U$26.D2 (D), U$26.D3 (D), U$26.D4 (D), U$26.D5 (D)
WAKE_1: U1.45 (PA12), WAKE_1_P.TP
WAKE_2: U1.40 (PC9), WAKE_2_P.TP
WAKE_3: U1.3 (PC14), WAKE_3_P.TP
WAKE_MID_1: U$21.47-WAKE (WAKE), WAKE_1.TP
WAKE_MID_2: U$3.47-WAKE (WAKE), WAKE_MID_2.TP
WAKE_MID_3: U$10.47-WAKE (WAKE), WAKE_MID_3.TP

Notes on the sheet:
drut do zaislnia
by zmniejszyc rezystancje sciezek
